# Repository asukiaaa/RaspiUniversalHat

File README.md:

# RaspiUniversalHat
A Raspberry Pi Hat for universal usage.

# License
MIT

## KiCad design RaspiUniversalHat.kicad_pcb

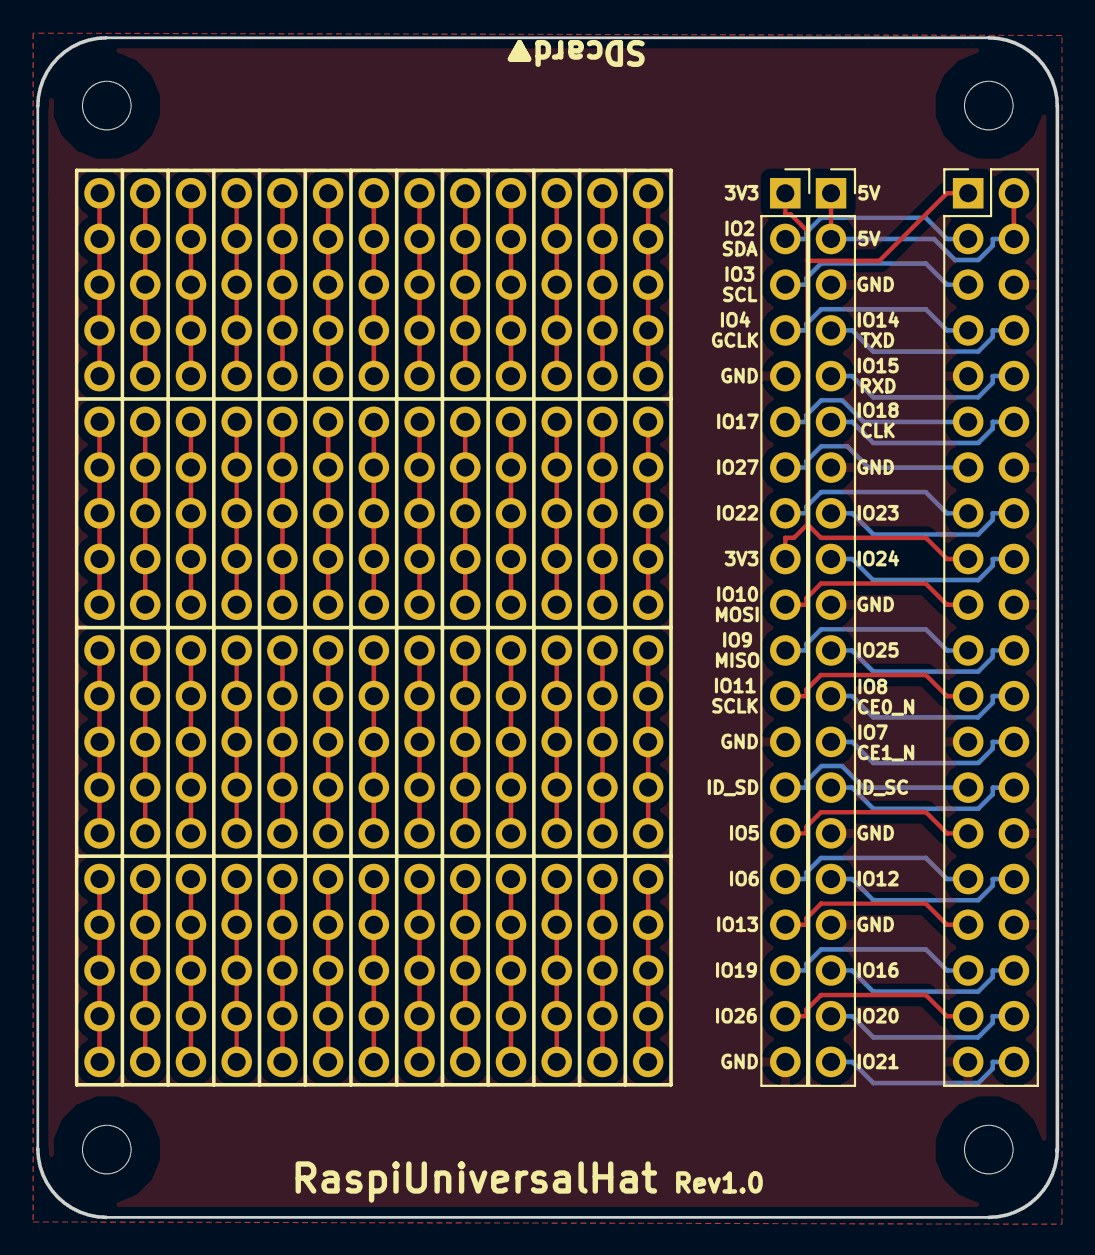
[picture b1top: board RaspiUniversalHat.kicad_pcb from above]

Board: 2 copper layers, 56.6 x 65.5 mm, 59 parts (0 on the bottom side), 83 nets.

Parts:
J1: Raspberry_Pi_2_3; PinHeader_2x20_P2.54mm_Vertical
J2, J3: Conn_01x20; PinSocket_1x20_P2.54mm_Vertical
J4, J5, J9, J10, J12, J13, J15, J16, J17, J18, J19, J21, J22, J23, J24, J25, J26, J27, J28, J29, J30, J32, J33, J34, J35, J36, J37, J38, J39, J40, J41, J42, J43, J44, J45, J46, J47, J48, J49, J50, J51, J52, J53, J54, J55, J57, J58, J59, J61, J62, J63, J64: Conn_01x05; NoMarkedPinSocket_1x05_P2.54mm
REF1, REF2, REF3, REF4: MountingHole_2.7mm; LargeClearanceMountingHole_2.7mm

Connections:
+3V3: J1.1, J1.17, J2.1, J2.9
+5C: J1.2, J1.4, J3.1, J3.2
GND: J1.6, J1.9, J1.14, J1.20, J1.25, J1.30, J1.34, J1.39, J2.5, J2.13, J2.20, J3.3, J3.7, J3.10, J3.15, J3.17
GPIO2(SDA1): J1.3, J2.2
GPIO3(SCL1): J1.5, J2.3
GPIO4(GCLK): J1.7, J2.4
GPIO5: J1.29, J2.15
GPIO6: J1.31, J2.16
GPIO7(SPI_CE1): J1.26, J3.13
GPIO8(SPI_CE0): J1.24, J3.12
GPIO9(SPI_MISO): J1.21, J2.11
GPIO10(SPI_MOSI): J1.19, J2.10
GPIO11(SPI_SCLK): J1.23, J2.12
GPIO12: J1.32, J3.16
GPIO13: J1.33, J2.17
GPIO14(TXD): J1.8, J3.4
GPIO15(RXD): J1.10, J3.5
GPIO16: J1.36, J3.18
GPIO17(GEN0): J1.11, J2.6
GPIO18(GEN1): J1.12, J3.6
GPIO19: J1.35, J2.18
GPIO20: J1.38, J3.19
GPIO21: J1.40, J3.20
GPIO22(GEN3): J1.15, J2.8
GPIO23(GEN4): J1.16, J3.8
GPIO24(GEN5): J1.18, J3.9
GPIO25(GEN6): J1.22, J3.11
GPIO26: J1.37, J2.19
GPIO27(GEN2): J1.13, J2.7
ID_SC: J1.28, J3.14
ID_SD: J1.27, J2.14
unnamed: J4.1, J4.2, J4.3, J4.4, J4.5
unnamed: J5.1, J5.2, J5.3, J5.4, J5.5
unnamed: J9.1, J9.2, J9.3, J9.4, J9.5
unnamed: J10.1, J10.2, J10.3, J10.4, J10.5
unnamed: J12.1, J12.2, J12.3, J12.4, J12.5
unnamed: J13.1, J13.2, J13.3, J13.4, J13.5
unnamed: J15.1, J15.2, J15.3, J15.4, J15.5
unnamed: J16.1, J16.2, J16.3, J16.4, J16.5
unnamed: J17.1, J17.2, J17.3, J17.4, J17.5
unnamed: J18.1, J18.2, J18.3, J18.4, J18.5
unnamed: J19.1, J19.2, J19.3, J19.4, J19.5
unnamed: J21.1, J21.2, J21.3, J21.4, J21.5
unnamed: J22.1, J22.2, J22.3, J22.4, J22.5
unnamed: J23.1, J23.2, J23.3, J23.4, J23.5
unnamed: J24.1, J24.2, J24.3, J24.4, J24.5
unnamed: J25.1, J25.2, J25.3, J25.4, J25.5
unnamed: J26.1, J26.2, J26.3, J26.4, J26.5
unnamed: J27.1, J27.2, J27.3, J27.4, J27.5
unnamed: J28.1, J28.2, J28.3, J28.4, J28.5
unnamed: J29.1, J29.2, J29.3, J29.4, J29.5
unnamed: J30.1, J30.2, J30.3, J30.4, J30.5
unnamed: J32.1, J32.2, J32.3, J32.4, J32.5
unnamed: J33.1, J33.2, J33.3, J33.4, J33.5
unnamed: J34.1, J34.2, J34.3, J34.4, J34.5
unnamed: J35.1, J35.2, J35.3, J35.4, J35.5
unnamed: J36.1, J36.2, J36.3, J36.4, J36.5
unnamed: J37.1, J37.2, J37.3, J37.4, J37.5
unnamed: J38.1, J38.2, J38.3, J38.4, J38.5
unnamed: J39.1, J39.2, J39.3, J39.4, J39.5
unnamed: J40.1, J40.2, J40.3, J40.4, J40.5
unnamed: J41.1, J41.2, J41.3, J41.4, J41.5
unnamed: J42.1, J42.2, J42.3, J42.4, J42.5
unnamed: J43.1, J43.2, J43.3, J43.4, J43.5
unnamed: J44.1, J44.2, J44.3, J44.4, J44.5
unnamed: J45.1, J45.2, J45.3, J45.4, J45.5
unnamed: J46.1, J46.2, J46.3, J46.4, J46.5
unnamed: J47.1, J47.2, J47.3, J47.4, J47.5
unnamed: J48.1, J48.2, J48.3, J48.4, J48.5
unnamed: J49.1, J49.2, J49.3, J49.4, J49.5
unnamed: J50.1, J50.2, J50.3, J50.4, J50.5
unnamed: J51.1, J51.2, J51.3, J51.4, J51.5
unnamed: J52.1, J52.2, J52.3, J52.4, J52.5
unnamed: J53.1, J53.2, J53.3, J53.4, J53.5
unnamed: J54.1, J54.2, J54.3, J54.4, J54.5
unnamed: J55.1, J55.2, J55.3, J55.4, J55.5
unnamed: J57.1, J57.2, J57.3, J57.4, J57.5
unnamed: J58.1, J58.2, J58.3, J58.4, J58.5
unnamed: J59.1, J59.2, J59.3, J59.4, J59.5
unnamed: J61.1, J61.2, J61.3, J61.4, J61.5
unnamed: J62.1, J62.2, J62.3, J62.4, J62.5
unnamed: J63.1, J63.2, J63.3, J63.4, J63.5
unnamed: J64.1, J64.2, J64.3, J64.4, J64.5

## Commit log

2018-04-18 Update text on silk
2018-04-23 Apply large clearance mounting holes
